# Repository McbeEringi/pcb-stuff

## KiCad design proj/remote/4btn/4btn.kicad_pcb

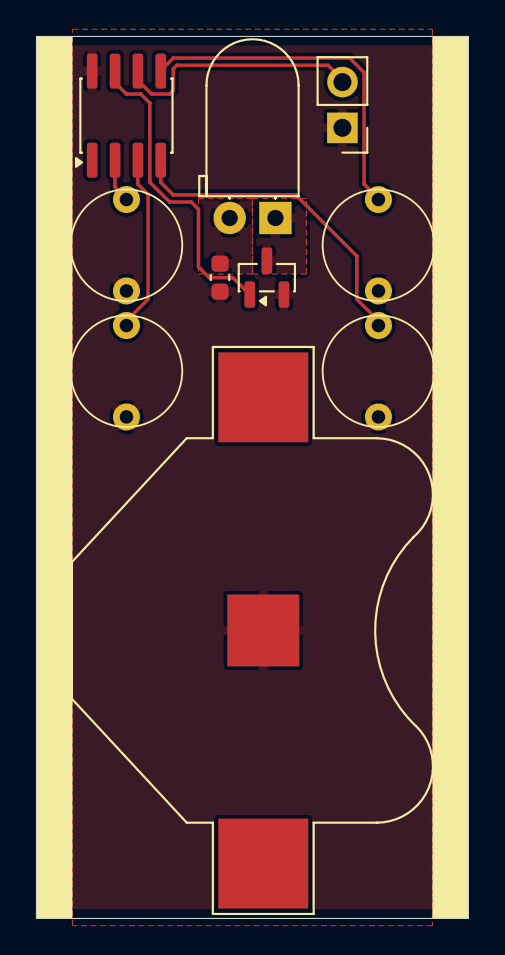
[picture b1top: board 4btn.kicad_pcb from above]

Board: 2 copper layers, 24.0 x 49.0 mm, 10 parts (0 on the bottom side), 9 nets.

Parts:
BT1: CR2032; BatteryHolder_Multicomp_BC-2001_1x2032
C1: 4u7; C_0603_1608Metric
D1: IR_LED; LED_D5.0mm_Horizontal_O1.27mm_Z3.0mm_Clear
J1: UPDI; PinHeader_1x02_P2.54mm_Vertical
Q1: BSS138; SOT-23
SW1: BTN1; alps-skrg
SW2: BTN2; alps-skrg
SW3: BTN6; alps-skrg
SW4: BTN7; alps-skrg
U1: ATtiny202-SS; SOIC-8_3.9x4.9mm_P1.27mm

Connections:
/LED: D1.1 (K), Q1.3 (D)
BTN1: SW1.1, U1.4 (PA1)
BTN2: SW2.1, U1.5 (PA2)
BTN6: SW3.1, U1.2 (PA6)
BTN7: SW4.1, U1.3 (PA7)
GND: BT1.2 (-), C1.2, J1.1, Q1.2 (S), SW1.2, SW2.2, SW3.2, SW4.2, U1.8 (GND)
UPDI: J1.2, U1.6 (~RESET/PA0)
VCC: BT1.1 (+), C1.1, D1.2 (A), U1.1 (VCC)
WO: Q1.1 (G), U1.7 (PA3)

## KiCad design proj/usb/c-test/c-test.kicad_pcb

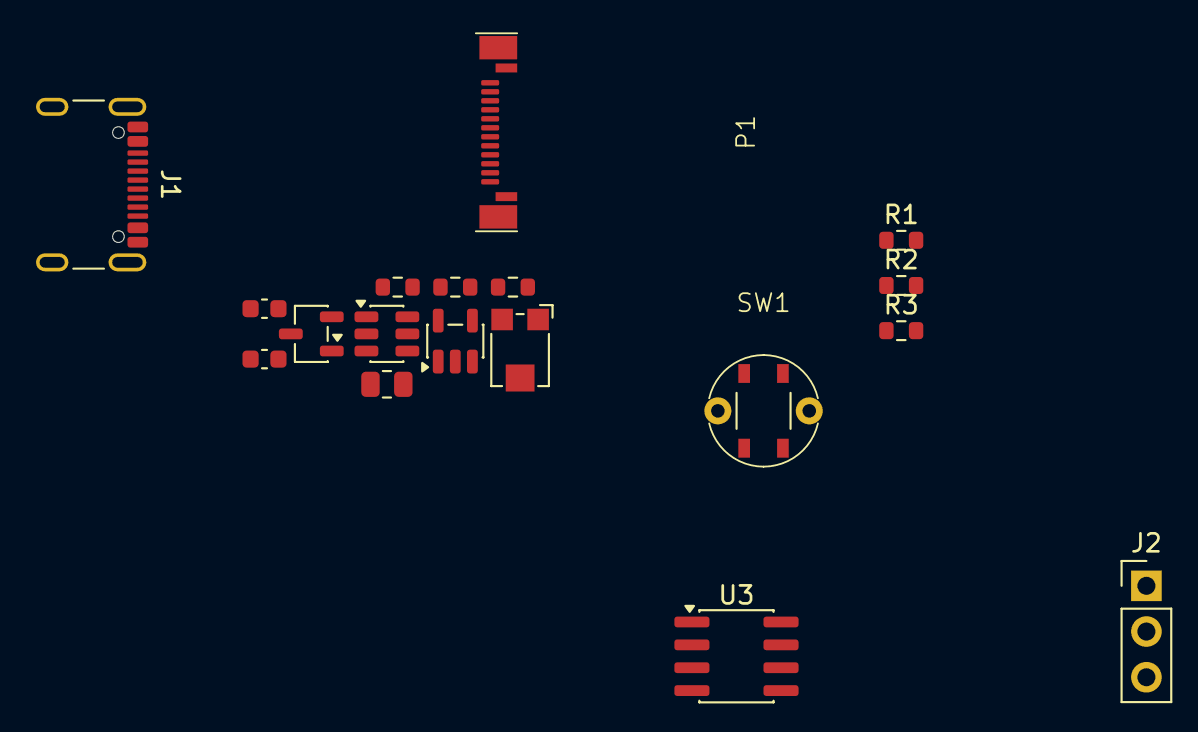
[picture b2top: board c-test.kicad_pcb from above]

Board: 2 copper layers, 18 parts (0 on the bottom side), 17 nets, no tracks yet.

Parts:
C1: 1u; C_0603_1608Metric
C2: 4u7; C_0603_1608Metric
J1: USB_C_Receptacle_USB2.0_16P; USB_C_Receptacle_GCT_USB4105-xx-A_16P_TopMnt_Horizontal
J2: Conn_01x03; PinHeader_1x03_P2.54mm_Vertical
P1: USB_C_Plug; USB_C_PLUG_00402-UCAM001-X
R1, R4, R5: 47k; R_0603_1608Metric
R2, R3: 10k; R_0603_1608Metric
R6: 56k; R_0603_1608Metric
R7: 8m; R_0805_2012Metric
RV1: 10k; Potentiometer_Bourns_TC33X_Vertical
SW1: SW_Push; alps-skr[gp]
U1: AP7375-33; SOT-23-3
U2: MCP6L91T-EOT; SOT-23-5
U3: ATtiny402-SS; SOIC-8_3.9x4.9mm_P1.27mm
U4: INA181; SOT-23-6

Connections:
+3V3: C2.1, R4.1, U1.2 (OUT), U2.5 (V+), U3.1 (VCC), U4.6 (V+)
CC1: J1.A5 (CC1), P1.A5 (CC)
D+: J1.A6 (D+), J1.B6 (D+), P1.A6 (D+)
D-: J1.A7 (D-), J1.B7 (D-), P1.A7 (D-)
GND: C1.2, C2.2, J1.A1 (GND), J1.A12 (GND), J1.B1 (GND), J1.B12 (GND), J1.SH (SHIELD), J2.2, P1.A1 (GND), P1.A12 (GND), P1.B12 (GND), R3.2, R6.2, SW1.2, U1.3 (GND), U2.2 (V-), U3.8 (GND), U4.2 (GND)
I_SENSE: U3.3 (PA7), U4.1
unnamed: R1.2, R2.1
unnamed: R4.2, R5.1
unnamed: R5.2, RV1.3
unnamed: R6.1, RV1.1
unnamed: RV1.2, U2.3 (+)
SHUNT: P1.A4 (VBUS), P1.B9 (VBUS), R7.2, U4.4 (-)
SOUT: J2.3, U3.2 (PA6)
UPDI: J2.1, U3.6 (~RESET/PA0)
VBUS: C1.1, J1.A4 (VBUS), J1.A9 (VBUS), J1.B4 (VBUS), J1.B9 (VBUS), R1.1, R7.1, U1.1 (IN), U4.3 (+)
VREF: U2.1, U2.4 (-), U4.5 (REF)
V_SENSE: R2.2, R3.1, SW1.1, U3.7 (PA3)

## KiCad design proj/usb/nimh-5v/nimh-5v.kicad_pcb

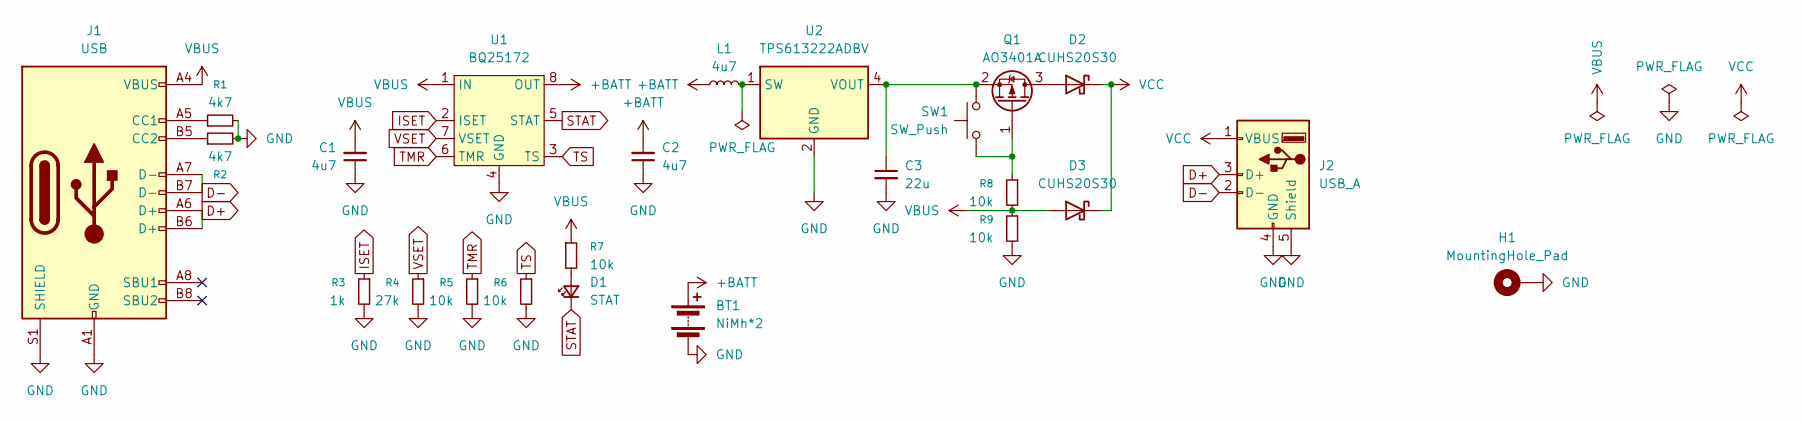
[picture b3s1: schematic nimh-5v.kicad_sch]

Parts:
BT1: NiMh*2; BH-321-1P_{24}
C1, C2: 4u7; C_0603_1608Metric
C3: 22u; C_0603_1608Metric
D1: STAT; LED_0603_1608Metric
D2, D3: CUHS20S30; US2H
H1: MountingHole_Pad; MountingHole_3.2mm_M3_Pad
J1: USB; USB_C_Receptacle_GCT_USB4105-xx-A_16P_TopMnt_Horizontal
J2: USB_A; USB_A_Molex_67643_Horizontal
L1: 4u7; L_1008_2520Metric
Q1: AO3401A; SOT-23
R1, R2: 4k7; R_0603_1608Metric
R3: 1k; R_0603_1608Metric
R4: 27k; R_0603_1608Metric
R5, R6, R7, R8, R9: 10k; R_0603_1608Metric
SW1: SW_Push; alps-skr[gp]
U1: BQ25172; WSON-8-1EP_2x2mm_P0.5mm_EP0.9x1.6mm
U2: TPS613222ADBV; SOT-23-5

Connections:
+BATT: BT1.1 (+), C2.2, L1.1, U1.8 (OUT)
D+: J1.A6 (D+), J1.B6 (D+), J2.3 (D+)
D-: J1.A7 (D-), J1.B7 (D-), J2.2 (D-)
GND: BT1.2 (-), C1.1, C2.1, C3.2, H1.1, J1.A1 (GND), J1.A12 (GND), J1.B1 (GND), J1.B12 (GND), J1.S1 (SHIELD), J2.4 (GND), J2.5 (Shield), R1.2, R2.2, R3.2, R4.2, R5.2, R6.2, R9.2, U1.4 (GND), U1.9 (GND), U2.2 (GND)
ISET: R3.1, U1.2 (ISET)
unnamed: D1.2 (A), R7.2
unnamed: D2.2 (A), Q1.3 (D)
unnamed: J1.A5 (CC1), R1.1
unnamed: J1.B5 (CC2), R2.1
unnamed: Q1.1 (G), R8.1, SW1.1
unnamed: C3.1, Q1.2 (S), SW1.2, U2.4 (VOUT)
unnamed: L1.2, U2.1 (SW)
STAT: D1.1 (K), U1.5 (STAT)
TMR: R5.1, U1.6 (TMR)
TS: R6.1, U1.3 (TS)
VBUS: C1.2, D3.2 (A), J1.A4 (VBUS), J1.A9 (VBUS), J1.B4 (VBUS), J1.B9 (VBUS), R7.1, R8.2, R9.1, U1.1 (IN)
VCC: D2.1 (K), D3.1 (K), J2.1 (VBUS)
VSET: R4.1, U1.7 (VSET)

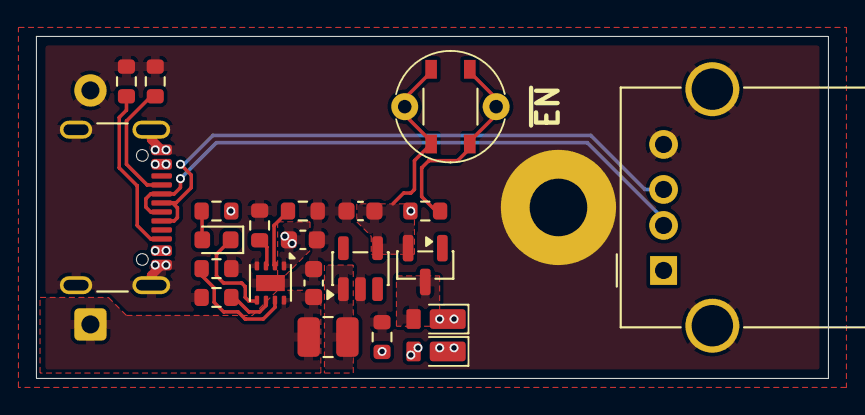
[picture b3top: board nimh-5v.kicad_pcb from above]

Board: 2 copper layers, 44.0 x 19.0 mm, 24 parts (1 on the bottom side), 18 nets.

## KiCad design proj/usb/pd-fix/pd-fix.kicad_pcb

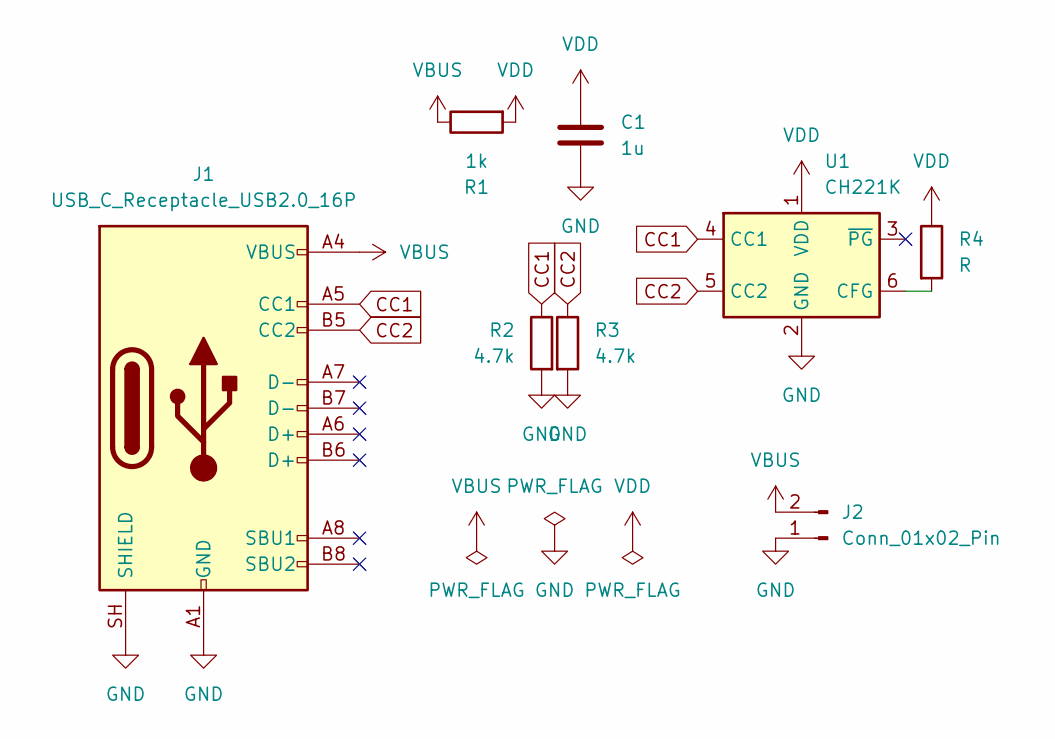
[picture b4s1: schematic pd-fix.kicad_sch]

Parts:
C1: 1u; C_0603_1608Metric
J1: USB_C_Receptacle_USB2.0_16P; USB_C_Receptacle_GCT_USB4105-xx-A_16P_TopMnt_Horizontal
J2: Conn_01x02_Pin; PinHeader_1x02_P2.54mm_Vertical
R1: 1k; R_0603_1608Metric
R2, R3: 4.7k; R_0603_1608Metric
R4: R; R_0603_1608Metric
U1: CH221K; SOT-23-6

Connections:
CC1: J1.A5 (CC1), R2.1, U1.4 (CC1)
CC2: J1.B5 (CC2), R3.1, U1.5 (CC2)
GND: C1.2, J1.A1 (GND), J1.A12 (GND), J1.B1 (GND), J1.B12 (GND), J1.SH (SHIELD), J2.1, R2.2, R3.2, U1.2 (GND)
unnamed: R4.2, U1.6 (CFG)
VBUS: J1.A4 (VBUS), J1.A9 (VBUS), J1.B4 (VBUS), J1.B9 (VBUS), J2.2, R1.1
VDD: C1.1, R1.2, R4.1, U1.1 (VDD)

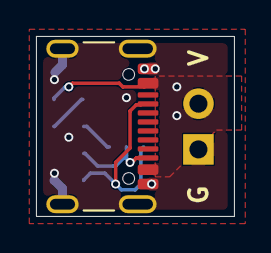
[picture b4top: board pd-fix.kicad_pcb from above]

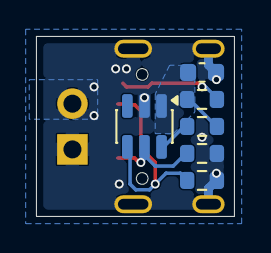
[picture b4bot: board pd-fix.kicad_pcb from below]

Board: 2 copper layers, 11.0 x 10.0 mm, 8 parts (6 on the bottom side), 6 nets.

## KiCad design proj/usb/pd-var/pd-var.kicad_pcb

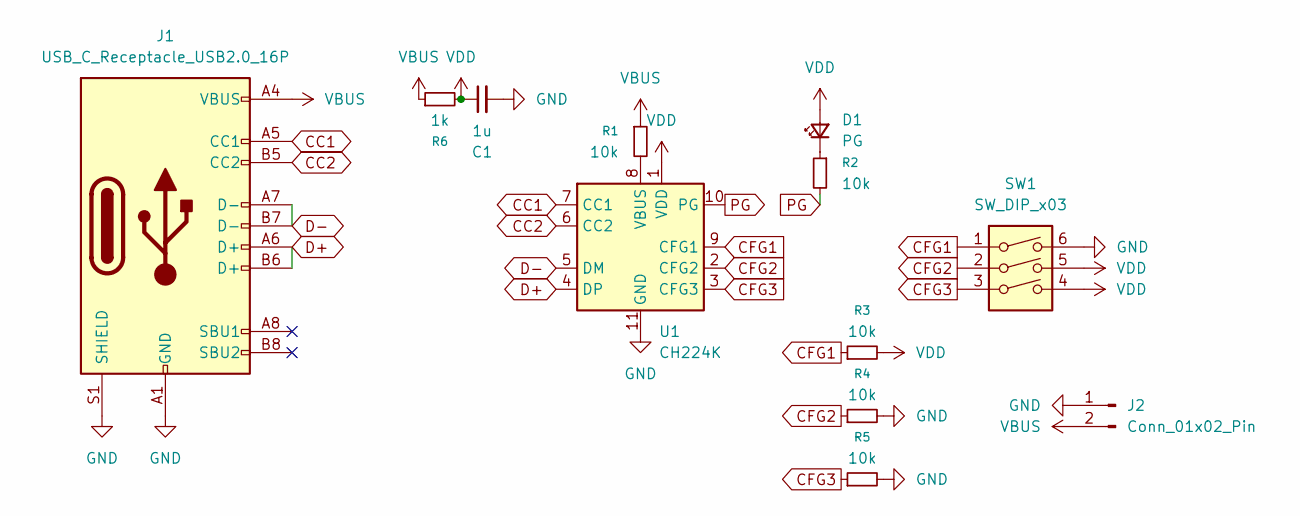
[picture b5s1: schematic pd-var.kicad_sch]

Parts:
C1: 1u; C_0603_1608Metric
D1: PG; LED_0603_1608Metric
J1: USB_C_Receptacle_USB2.0_16P; USB_C_Receptacle_GCT_USB4105-xx-A_16P_TopMnt_Horizontal
J2: Conn_01x02_Pin; SolderPad_2P
R1, R2, R3, R4, R5: 10k; R_0603_1608Metric
R6: 1k; R_0603_1608Metric
SW1: SW_DIP_x03; DIP-6_W7.62mm
U1: CH224K; SSOP-10-1EP_3.9x4.9mm_P1mm_EP2.1x3.3mm

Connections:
CC1: J1.A5 (CC1), U1.7 (CC1)
CC2: J1.B5 (CC2), U1.6 (CC2)
CFG1: R3.1, SW1.1, U1.9 (CFG1)
CFG2: R4.1, SW1.2, U1.2 (CFG2)
CFG3: R5.1, SW1.3, U1.3 (CFG3)
D+: J1.A6 (D+), J1.B6 (D+), U1.4 (DP)
D-: J1.A7 (D-), J1.B7 (D-), U1.5 (DM)
GND: C1.2, J1.A1 (GND), J1.A12 (GND), J1.B1 (GND), J1.B12 (GND), J1.S1 (SHIELD), J2.1, R4.2, R5.2, SW1.6, U1.11 (GND)
unnamed: D1.1 (K), R2.1
unnamed: R1.2, U1.8 (VBUS)
PG: R2.2, U1.10 (PG)
VBUS: J1.A4 (VBUS), J1.A9 (VBUS), J1.B4 (VBUS), J1.B9 (VBUS), J2.2, R1.1, R6.1
VDD: C1.1, D1.2 (A), R3.2, R6.2, SW1.4, SW1.5, U1.1 (VDD)

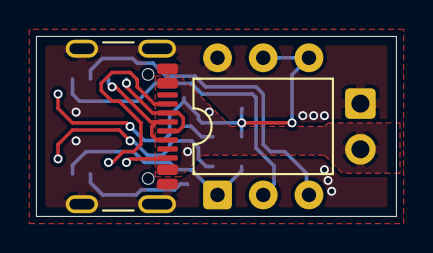
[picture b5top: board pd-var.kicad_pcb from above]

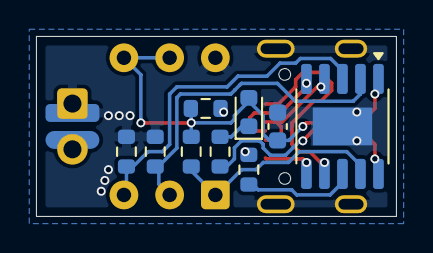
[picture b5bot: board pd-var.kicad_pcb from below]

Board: 2 copper layers, 20.0 x 10.0 mm, 12 parts (10 on the bottom side), 13 nets.

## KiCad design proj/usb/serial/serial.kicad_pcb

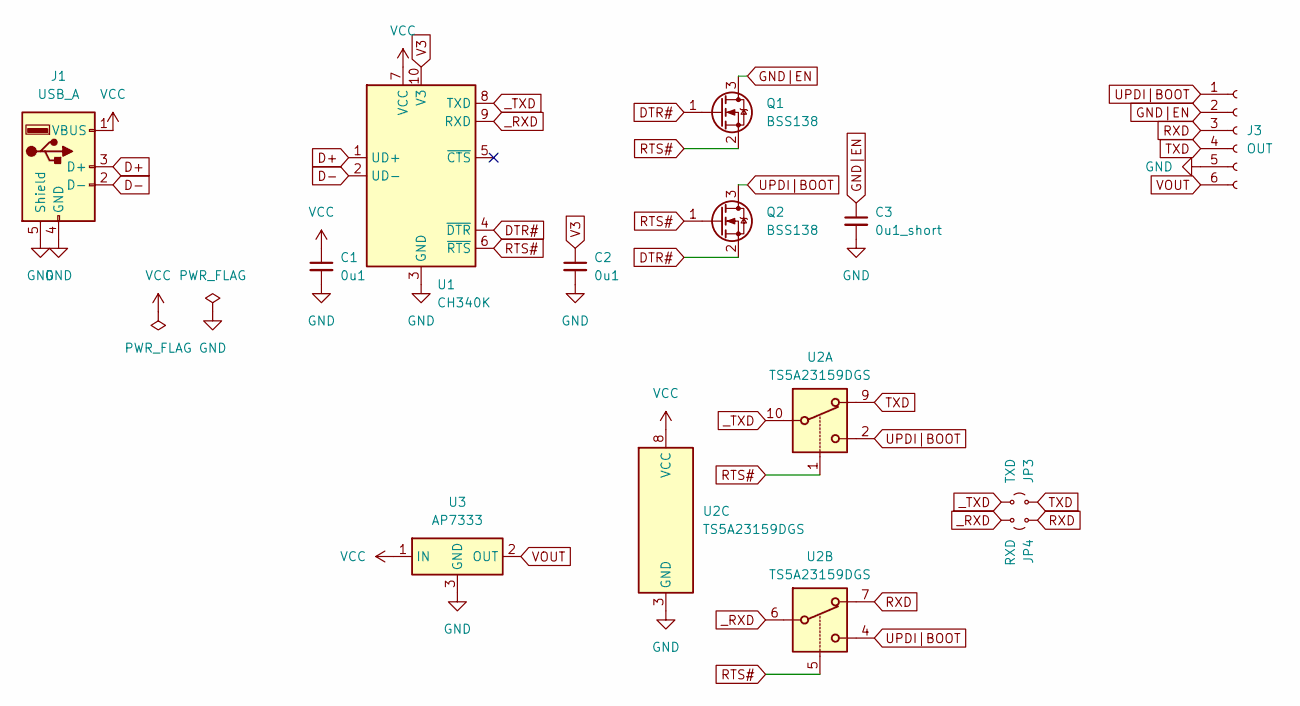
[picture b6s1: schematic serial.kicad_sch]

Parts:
C1, C2: 0u1; C_0603_1608Metric
C3: 0u1_short; C_0603_1608Metric
J1: USB_A; USB_A_PLUG_USB-4AM103AS
J3: OUT; PinSocket_1x06_P2.54mm_Vertical
JP3: TXD; R_0603_1608Metric
JP4: RXD; R_0603_1608Metric
Q1, Q2: BSS138; SOT-23
U1: CH340K; SSOP-10-1EP_3.9x4.9mm_P1mm_EP2.1x3.3mm
U2: TS5A23159DGS; VSSOP-10_3x3mm_P0.5mm
U3: AP7333; SOT-23-3

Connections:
D+: J1.3 (D+), U1.1 (UD+)
D-: J1.2 (D-), U1.2 (UD-)
DTR#: Q1.1 (G), Q2.2 (S), U1.4 (~DTR)
GND: C1.2, C2.2, C3.2, J1.4 (GND), J1.5 (Shield), J3.5, U1.3 (GND), U2.3 (GND), U3.3 (GND)
GND|EN: C3.1, J3.2, Q1.3 (D)
RTS#: Q1.2 (S), Q2.1 (G), U1.6 (~RTS), U2.1, U2.5
RXD: J3.3, JP4.2 (B), U2.7
TXD: J3.4, JP3.2 (B), U2.9
UPDI|BOOT: J3.1, Q2.3 (D), U2.2, U2.4
V3: C2.1, U1.10 (V3)
VCC: C1.1, J1.1 (VBUS), U1.7 (VCC), U2.8 (VCC), U3.1 (IN)
VOUT: J3.6, U3.2 (OUT)
_RXD: JP4.1 (A), U1.9 (RXD), U2.6
_TXD: JP3.1 (A), U1.8 (TXD), U2.10

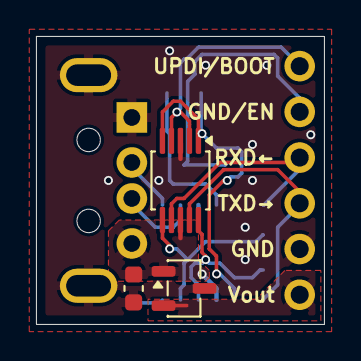
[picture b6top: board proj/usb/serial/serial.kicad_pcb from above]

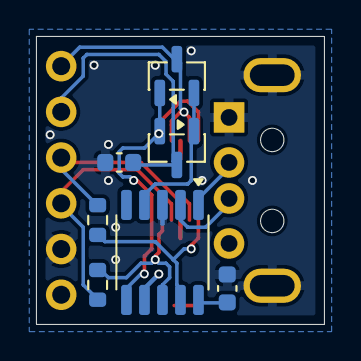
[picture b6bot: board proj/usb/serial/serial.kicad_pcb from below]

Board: 2 copper layers, 16.0 x 16.0 mm, 12 parts (7 on the bottom side), 14 nets.

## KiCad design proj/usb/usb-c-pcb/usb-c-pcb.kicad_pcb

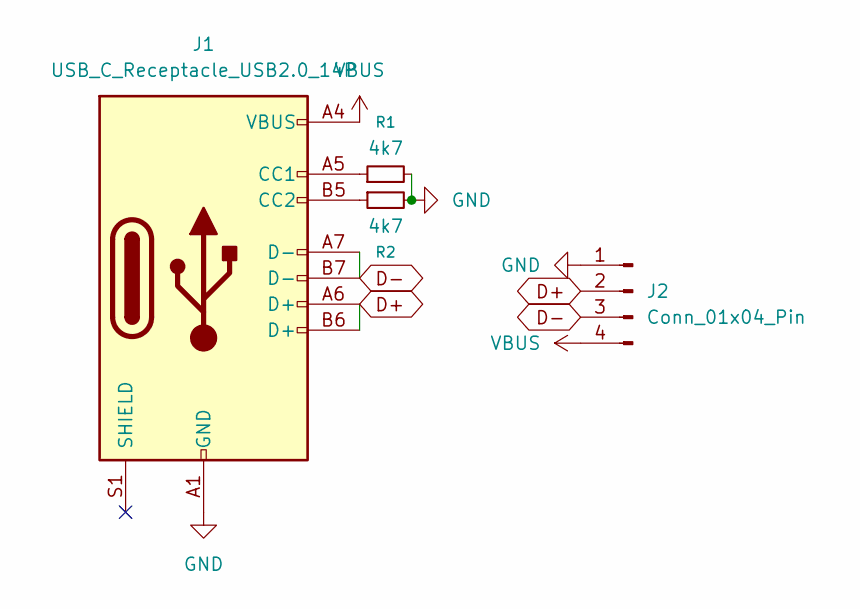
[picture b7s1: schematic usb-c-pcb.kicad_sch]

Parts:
J1: USB_C_Receptacle_USB2.0_14P; USB-C
J2: Conn_01x04_Pin; PinHeader_1x04_P2.54mm_Vertical
R1, R2: 4k7; R_0603_1608Metric

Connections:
D+: J1.A6 (D+), J1.B6 (D+), J2.2
D-: J1.A7 (D-), J1.B7 (D-), J2.3
GND: J1.A1 (GND), J1.A12 (GND), J1.B1 (GND), J1.B12 (GND), J2.1, R1.2, R2.2
unnamed: J1.A5 (CC1), R1.1
unnamed: J1.B5 (CC2), R2.1
VBUS: J1.A4 (VBUS), J1.A9 (VBUS), J1.B4 (VBUS), J1.B9 (VBUS), J2.4

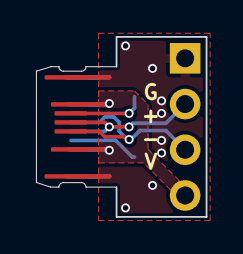
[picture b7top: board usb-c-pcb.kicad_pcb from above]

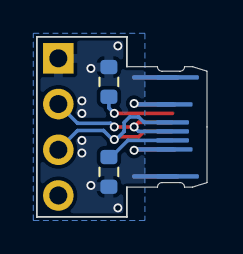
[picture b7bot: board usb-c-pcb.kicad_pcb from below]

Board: 2 copper layers, 9.5 x 10.0 mm, 4 parts (3 on the bottom side), 6 nets.

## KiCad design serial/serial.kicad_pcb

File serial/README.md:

# CH340K USBシリアル変換モジュール
CH340Kを用いたUSBシリアル変換モジュール
## 特徴
- 安価
	- 高々￥150
- 高速
	- 1.5Mbps
- 幅広い対象電圧
	- 5V, 3.3V, 2.5V, 1.8V
	- 切り替え不要
	- 恐らくその他電圧も
- ESP32向け自動書き込み回路付き
## 用途
- ESP32の書き込み(自動書き込み回路付き)
- UARTの読み書き
- AVRのserialupdi書き込み機
## 部品
- [CH340K](https://akizukidenshi.com/catalog/g/gI-16306/) *1
- [BSS138](https://akizukidenshi.com/catalog/g/gI-04232/) *2
- [1608サイズ 0.1uF](https://akizukidenshi.com/catalog/g/gP-13374/) *3
## ピン配置
信号線はトレラントだが**電源は5V**なので注意
```
IO0 EN  5V
TXD RXD GND
```
```
-----------------
|               |
|USB         USB|
|USB USB USB USB|
|USB USB USB USB|
|USB USB USB USB|
|               |
| icicic cap fet|
| icicic        |
| icicic cap fet|
|            cap|
|IO0 EN  5V     |
|TXD RXD GND    |
-----------------
```
ESPに書き込む場合はTXD,RXDのみ反転
AVRに書き込む場合はTXD,RXDをまとめてUPDIとする(抵抗もダイオードも不要)
## ドライバ(Windowsのみ)
CH340シリーズはWindowsで使う場合ドライバのインストールが必要
[WCH公式 CH340](https://www.wch-ic.com/products/CH340.html)のCH341SER.EXEを入れる

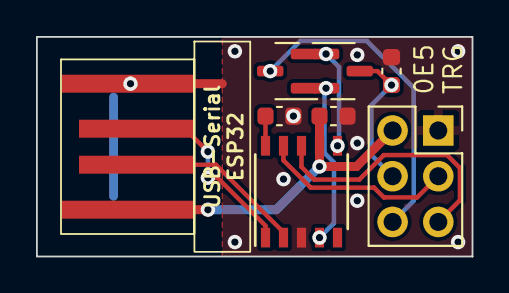
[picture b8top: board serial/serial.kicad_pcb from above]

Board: 2 copper layers, 24.2 x 12.2 mm, 8 parts (0 on the bottom side), 11 nets.

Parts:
0u1, 0u1 x3, 0u1#2: 0.1u; C_0603_1608Metric
BSS138 x2: BSS138; SOT-23
CH340K: CH340K; SSOP-10_3.9x4.9mm_P1.00mm
J2: Conn_02x03_Odd_Even; PinSocket_2x03_P2.54mm_Vertical
Q1: BSS138; SOT-23
U2: PCB_USB_Conn

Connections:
unnamed: 0u1.2, 0u1 x3.2, 0u1#2.2, CH340K.3 (GND), J2.1, U2.1 (GND), U2.5 (SHIELD), U2.6 (SHIELD)
unnamed: 0u1.1, CH340K.7 (VCC), J2.2, U2.4 (VBUS)
unnamed: CH340K.9 (RXD), J2.3
unnamed: 0u1#2.1, J2.4, Q1.3 (D)
unnamed: CH340K.8 (TXD), J2.5
unnamed: BSS138 x2.3 (D), J2.6
unnamed: BSS138 x2.2 (S), CH340K.6 (RTS#), Q1.1 (G)
unnamed: BSS138 x2.1 (G), CH340K.4 (DTR#), Q1.2 (S)
unnamed: CH340K.1 (UD+), U2.2 (D+)
unnamed: CH340K.2 (UD-), U2.3 (D-)
unnamed: 0u1 x3.1, CH340K.10 (V3)

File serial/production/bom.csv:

Designator,Footprint,Quantity,Value,LCSC Part #
"0u1_2, 0u1, 0u1 x3",0603,3,0.1u,
"BSS138 x2, Q1",SOT-23,2,BSS138,
CH340K,SSOP-10_3.9x4.9mm_P1.00mm,1,CH340K,
J2,PinSocket_2x03_P2.54mm_Vertical,1,Conn_02x03_Odd_Even,
U2,PCB_USB_Conn,1,~,
